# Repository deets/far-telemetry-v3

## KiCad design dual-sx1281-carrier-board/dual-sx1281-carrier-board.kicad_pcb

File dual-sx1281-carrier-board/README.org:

#+STARTUP: inlineimages showall
* Dual Carrier Board

[[file:assets/dual-sx1281-carrier-board.png]]

** PCB
*** Aisler

 - [[https://community.aisler.net/t/2-layer-1-6mm-35-m-enig-design-rules/3732][Design rules]].

** Breadboard Setup

*** E28-2G4M20SX

|------------+---------------------+----------|
| Module Pin | Breakout Pin Number | Function |
|------------+---------------------+----------|
|          1 |                  17 | 3V3      |
|          2 |                  18 | GND      |
|          3 |                  19 | SPI TX   |
|          4 |                  20 | SPI RX   |
|          5 |                  21 | SPI CLK  |
|          6 |                  22 | SPI CS   |
|          7 |                  23 | GND      |
|          8 |                  24 | RX_EN    |
|          9 |                   1 | TX_EN    |
|         10 |                   2 | GND      |
|         11 |                   3 | NRST     |
|         12 |                   4 | BUSY     |
|         13 |                   5 | IRQ      |
|         14 |                   6 | X        |
|         15 |                   7 | X        |
|         16 |                   8 | GND      |
|------------+---------------------+----------|

*** RP2040/PicoW

|------------+-----------+-------------|
| RP2040 GIO | PicoW Pin | Function    |
|------------+-----------+-------------|
|          2 |         4 | SPI0_CLK    |
|          3 |         5 | SPI0_TX     |
|          4 |         6 | SPI0_RX     |
|          5 |         7 | SPI0_CS     |
|          6 |         9 | LORA1_IRQ   |
|          7 |        10 | LORA1_BUSY  |
|          8 |        11 | LORA1_NRST  |
|          9 |        12 | LORA1_TX_EN |
|         10 |        14 | LORA1_RX_EN |
|------------+-----------+-------------|
|         11 |        15 | SPI1_TX     |
|         12 |        16 | SPI1_RX     |
|         13 |        17 | SPI1_CS     |
|         14 |        19 | SPI1_CLK    |
|         15 |        20 | LORA2_RX_EN |
|         16 |        21 | LORA2_IRQ   |
|         17 |        22 | LORA2_BUSY  |
|         18 |        24 | LORA2_NRST  |
|         19 |        25 | LORA2_TX_EN |
|------------+-----------+-------------|

[[file:assets/picow-pinout.svg]]

*** lora-phy driver implementation

**** RadioLib commands

OpCode: GetPacketType -> [03, 00, 00, ]
OpCode: GetPacketType -> [03, 00, 00, ]
OpCode: ReadRegister -> [19, 09, 3C, 00, 00, ]
OpCode: GetStatus -> [C0, 00, 00, ]
OpCode: GetPacketType -> [03, 00, 00, ]
OpCode: GetPacketType -> [03, 00, 00, ]
OpCode: GetPacketType -> [03, 00, 00, ]
OpCode: SetPacketParams -> [8C, 14, 00, FF, 20, 40, 00, 00, ]
success!
[SX1280] Transmitting packet ... OpCode: GetPacketType -> [03, 00, 00, ]
OpCode: NoOp -> [00, ]
OpCode: SetStandby -> [80, 00, ]
OpCode: GetPacketType -> [03, 00, 00, ]
OpCode: GetPacketType -> [03, 00, 00, ]
OpCode: SetPacketParams -> [8C, 14, 00, 0F, 20, 40, 00, 00, ]
OpCode: SetTxParams -> [8E, 1C, 80, ]
OpCode: SetBufferBaseAddress -> [8F, 00, 00, ]
OpCode: WriteBuffer -> [1A, 00, 48, 65, 6C, 6C, 6F, 20, 57, 6F, 72, 6C, 64, 21, 20, 23, 30, ]
OpCode: SetDioIrqParams -> [8D, 40, 01, 00, 01, 00, 00, 00, 00, ]
OpCode: SetTx -> [83, 00, 00, 00, ]

**** lora-phy translation

***** impl Lora<RK, DLY>::init

  - [X] reset
  - [X] ensure_ready
  - [X] set_standby
  - [ ] ensure_ready can't read the FirmwareVersions string, as it's used later as well. Try and make it work after reset or so.

***** impl Lora<RK, DLY>::prepare_for_tx

    - [X] self.prepare_modem(mdltn_params.frequency_in_hz).await?;
    - [X] self.radio_kind.set_modulation_params(mdltn_params).await?;
    - [ ] self.radio_kind.set_tx_power_and_ramp_time(output_power, Some(mdltn_params), true).await?;
    - [ ] self.radio_kind.ensure_ready(self.radio_mode).await?;
    - [ ] if self.radio_mode != RadioMode::Standby { self.radio_kind.set_standby().await?; self.radio_mode = RadioMode::Standby;  }
    - [ ] tx_pkt_params.set_payload_length(buffer.len())?;
    - [ ] self.radio_kind.set_packet_params(tx_pkt_params).await?;
    - [ ] self.radio_kind.set_channel(mdltn_params.frequency_in_hz).await?;
    - [ ] self.radio_kind.set_payload(buffer).await?;
    - [ ] self.radio_mode = RadioMode::Transmit;
    - [ ] self.radio_kind.set_irq_params(Some(self.radio_mode)).await?;

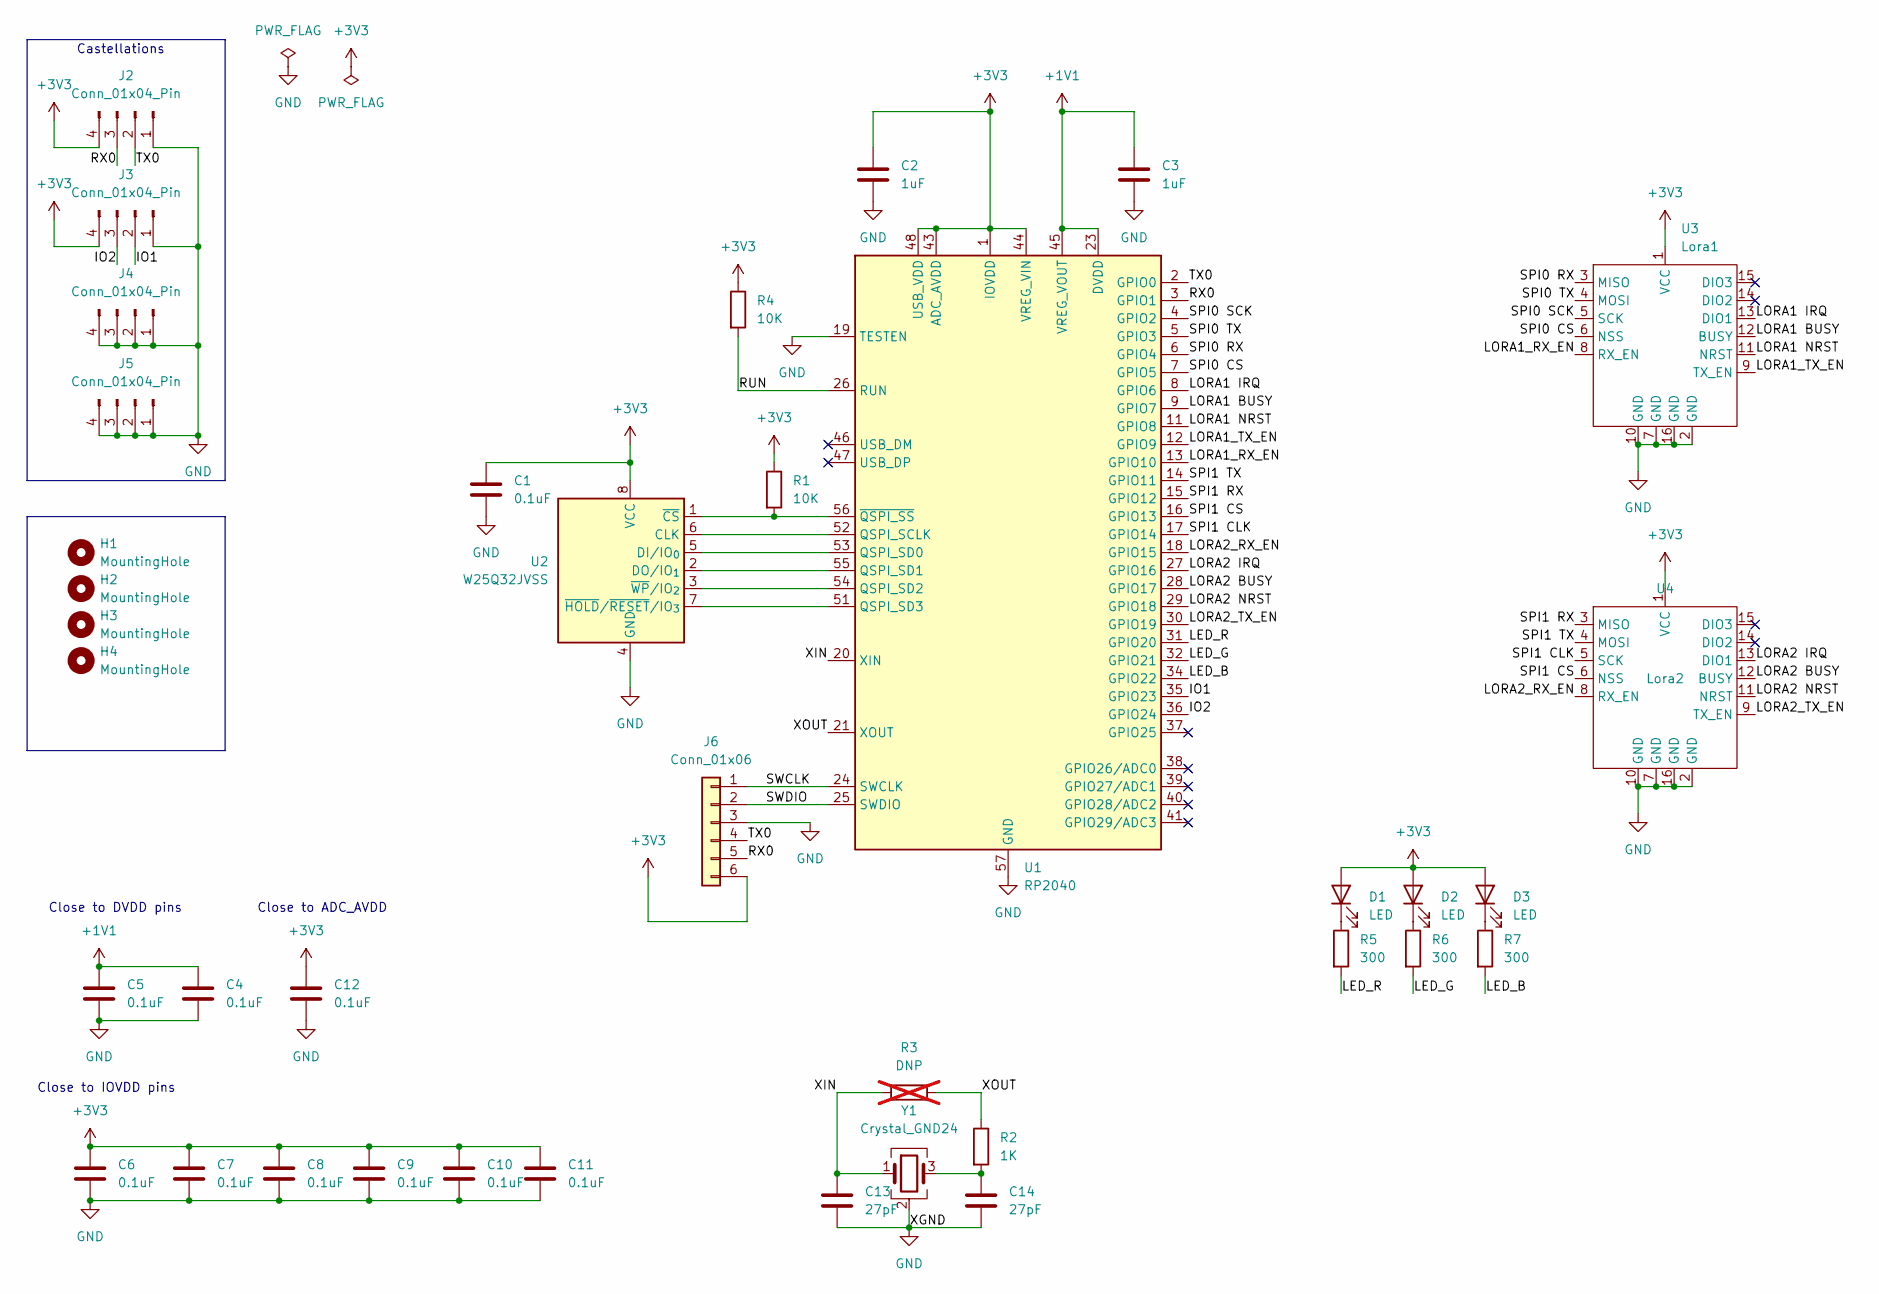
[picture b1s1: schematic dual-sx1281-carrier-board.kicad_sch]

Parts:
C1, C4, C5, C6, C7, C8, C9, C10, C11, C12: 0.1uF; C_0603_1608Metric
C2, C3: 1uF; C_0603_1608Metric
C13, C14: 27pF; C_0603_1608Metric
D1, D2, D3: LED; LED_0603_1608Metric
H1, H2, H3, H4: MountingHole; MountingHole_2mm
J2, J3, J4, J5: Conn_01x04_Pin; PinHeader_1x04_P2.54mm_Vertical
J6: Conn_01x06; Molex_PicoBlade_53398-0671_1x06-1MP_P1.25mm_Vertical
R1: 10K; R_0402_1005Metric
R2: 1K; R_0402_1005Metric
R3: DNP; R_0402_1005Metric; not fitted
R4: 10K; R_0603_1608Metric
R5, R6, R7: 300; R_0603_1608Metric
U1: RP2040; QFN-56-1EP_7x7mm_P0.4mm_EP3.2x3.2mm
U2: W25Q32JVSS; SOIC-8_5.3x5.3mm_P1.27mm
U3, U4: E28-2G4M20SX
Y1: Crystal_GND24; Crystal_SMD_3225-4Pin_3.2x2.5mm

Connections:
+1V1: C3.1, C4.1, C5.1, U1.23 (DVDD), U1.45 (VREG_VOUT), U1.50 (DVDD)
+3V3: C1.1, C2.1, C6.1, C7.1, C8.1, C9.1, C10.1, C11.1, C12.1, D1.2 (A), D2.2 (A), D3.2 (A), J2.4, J3.4, J6.6, R1.1, R4.1, U1.1 (IOVDD), U1.10 (IOVDD), U1.22 (IOVDD), U1.33 (IOVDD), U1.42 (IOVDD), U1.43 (ADC_AVDD), U1.44 (VREG_VIN), U1.48 (USB_VDD), U1.49 (IOVDD), U2.8 (VCC), U3.1 (VCC), U4.1 (VCC)
/IO1: J3.2, U1.35 (GPIO23)
/IO2: J3.3, U1.36 (GPIO24)
/LED_B: R7.2, U1.34 (GPIO22)
/LED_G: R6.2, U1.32 (GPIO21)
/LED_R: R5.2, U1.31 (GPIO20)
/LORA1 BUSY: U1.9 (GPIO7), U3.12 (BUSY)
/LORA1 IRQ: U1.8 (GPIO6), U3.13 (DIO1)
/LORA1 NRST: U1.11 (GPIO8), U3.11 (NRST)
/LORA1_RX_EN: U1.13 (GPIO10), U3.8 (RX_EN)
/LORA1_TX_EN: U1.12 (GPIO9), U3.9 (TX_EN)
/LORA2 BUSY: U1.28 (GPIO17), U4.12 (BUSY)
/LORA2 IRQ: U1.27 (GPIO16), U4.13 (DIO1)
/LORA2 NRST: U1.29 (GPIO18), U4.11 (NRST)
/LORA2_RX_EN: U1.18 (GPIO15), U4.8 (RX_EN)
/LORA2_TX_EN: U1.30 (GPIO19), U4.9 (TX_EN)
/RUN: R4.2, U1.26 (RUN)
/RX0: J2.3, J6.5, U1.3 (GPIO1)
/SPI0 CS: U1.7 (GPIO5), U3.6 (NSS)
/SPI0 RX: U1.6 (GPIO4), U3.3 (MISO)
/SPI0 SCK: U1.4 (GPIO2), U3.5 (SCK)
/SPI0 TX: U1.5 (GPIO3), U3.4 (MOSI)
/SPI1 CLK: U1.17 (GPIO14), U4.5 (SCK)
/SPI1 CS: U1.16 (GPIO13), U4.6 (NSS)
/SPI1 RX: U1.15 (GPIO12), U4.3 (MISO)
/SPI1 TX: U1.14 (GPIO11), U4.4 (MOSI)
/SWCLK: J6.1, U1.24 (SWCLK)
/SWDIO: J6.2, U1.25 (SWDIO)
/TX0: J2.2, J6.4, U1.2 (GPIO0)
/XIN: C13.1, R3.1, U1.20 (XIN), Y1.1
/XOUT: R2.1, R3.2, U1.21 (XOUT)
GND: C1.2, C2.2, C3.2, C4.2, C5.2, C6.2, C7.2, C8.2, C9.2, C10.2, C11.2, C12.2, C13.2, C14.2, J2.1, J3.1, J4.1, J4.2, J4.3, J4.4, J5.1, J5.2, J5.3, J5.4, J6.3, U1.19 (TESTEN), U1.57 (GND), U2.4 (GND), U3.2 (GND), U3.7 (GND), U3.10 (GND), U3.16 (GND), U4.2 (GND), U4.7 (GND), U4.10 (GND), U4.16 (GND), Y1.2 (G), Y1.4 (G)
unnamed: C14.1, R2.2, Y1.3
unnamed: D1.1 (K), R5.1
unnamed: D2.1 (K), R6.1
unnamed: D3.1 (K), R7.1
unnamed: U1.52 (QSPI_SCLK), U2.6 (CLK)
unnamed: U1.53 (QSPI_SD0), U2.5 (DI/IO_{0})
unnamed: U1.55 (QSPI_SD1), U2.2 (DO/IO_{1})
unnamed: U1.54 (QSPI_SD2), U2.3 (~WP/IO_{2})
unnamed: U1.51 (QSPI_SD3), U2.7 (~HOLD/~RESET/IO_{3})
unnamed: R1.2, U1.56 (~QSPI_SS), U2.1 (~CS)

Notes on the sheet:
Castellations
Close to ADC_AVDD
Close to DVDD pins
Close to IOVDD pins

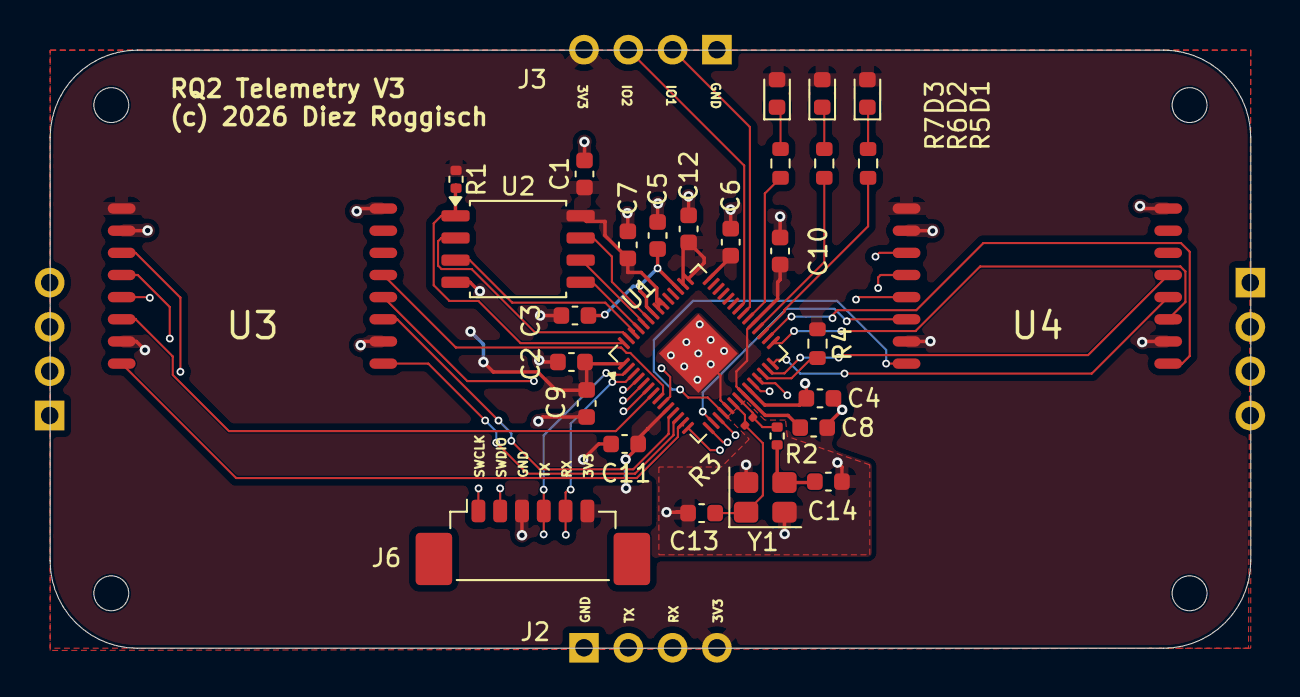
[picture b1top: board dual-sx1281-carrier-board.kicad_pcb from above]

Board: 4 copper layers, 68.8 x 34.3 mm, 38 parts (0 on the bottom side), 43 nets.

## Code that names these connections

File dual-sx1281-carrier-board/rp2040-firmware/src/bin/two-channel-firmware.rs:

//! This example runs on the Raspberry Pi Pico with a Waveshare board containing a Semtech Sx1262 radio.
//! It demonstrates LORA P2P send functionality.

#![no_std]
#![no_main]

use defmt::*;
use dual_sx1281_carrier_board::MessageType;
use dual_sx1281_carrier_board::{
    host_interface::uart_task, lora1_task, lora2_task, LORA1_PAYLOAD_RECEIVE_CHANNEL,
    LORA1_PAYLOAD_SEND_CHANNEL, LORA1_RECEIVE_CHANNEL, LORA1_SEND_CHANNEL,
    LORA2_PAYLOAD_RECEIVE_CHANNEL, LORA2_PAYLOAD_SEND_CHANNEL, LORA2_RECEIVE_CHANNEL,
    LORA2_SEND_CHANNEL,
};
use embassy_executor::Spawner;
use embassy_rp::bind_interrupts;
use embassy_rp::gpio::{Input, Level, Output, Pin, Pull};
use embassy_rp::peripherals::UART0;
use embassy_rp::spi::{Config, Spi};
use embassy_rp::uart::{Config as UartConfig, InterruptHandler, Uart};
use embassy_sync::blocking_mutex::raw::NoopRawMutex;
use embassy_sync::channel::Channel;
use embassy_time::{Delay, Timer};
use embedded_hal_bus::spi::ExclusiveDevice;
use lora_phy::iv::GenericSx128xInterfaceVariant;
use lora_phy::sx128x::{self, Sx1281, Sx128x};
use lora_phy::LoRa;
use rq2_telemetry_parser::Command;
use {defmt_rtt as _, panic_probe as _};

bind_interrupts!(struct Irqs {
    UART0_IRQ => InterruptHandler<UART0>;
});

#[embassy_executor::main]
async fn main(spawner: Spawner) {
    info!("running");
    let p = embassy_rp::init(Default::default());

    let lora1_nss = Output::new(p.PIN_5.degrade(), Level::High);
    let lora1_busy = Input::new(p.PIN_7.degrade(), Pull::None);
    let lora1_reset = Output::new(p.PIN_8.degrade(), Level::High);
    let lora1_irq = Input::new(p.PIN_6.degrade(), Pull::None);
    let lora1_rx_en = Output::new(p.PIN_10.degrade(), Level::Low);
    let lora1_tx_en = Output::new(p.PIN_9.degrade(), Level::Low);

    let (tx_pin, rx_pin, uart) = (p.PIN_0, p.PIN_1, p.UART0);
    let uart = Uart::new(
        uart,
        tx_pin,
        rx_pin,
        Irqs,
        p.DMA_CH4,
        p.DMA_CH5,
        UartConfig::default(),
    );

    let lora1_spi = Spi::new(
        p.SPI0,
        p.PIN_2,
        p.PIN_3,
        p.PIN_4,
        p.DMA_CH0,
        p.DMA_CH1,
        Config::default(),
    );
    let lora1_spi = ExclusiveDevice::new(lora1_spi, lora1_nss, Delay);
    let lora1_config = sx128x::Config {
        chip: Sx1281,
        tcxo_used: true,
        rx_boost: true,
        tx_boost: true,
    };
    let lora1_iv = GenericSx128xInterfaceVariant::new(
        lora1_reset,
        lora1_irq,
        lora1_busy,
        Some(lora1_rx_en),
        Some(lora1_tx_en),
    )
    .unwrap();
    let lora1 = LoRa::new(Sx128x::new(lora1_spi, lora1_iv, lora1_config), false, Delay)
        .await
        .unwrap();
    info!("Created lora1");

    let lora2_nss = Output::new(p.PIN_13.degrade(), Level::High);
    let lora2_busy = Input::new(p.PIN_17.degrade(), Pull::None);
    let lora2_reset = Output::new(p.PIN_18.degrade(), Level::High);
    let lora2_irq = Input::new(p.PIN_16.degrade(), Pull::None);
    let lora2_rx_en = Output::new(p.PIN_15.degrade(), Level::Low);
    let lora2_tx_en = Output::new(p.PIN_19.degrade(), Level::Low);

    let lora2_spi = Spi::new(
        p.SPI1,
        p.PIN_14,
        p.PIN_11,
        p.PIN_12,
        p.DMA_CH2,
        p.DMA_CH3,
        Config::default(),
    );

    let lora2_spi = ExclusiveDevice::new(lora2_spi, lora2_nss, Delay);
    let lora2_config = sx128x::Config {
        chip: Sx1281,
        tcxo_used: true,
        rx_boost: true,
        tx_boost: true,
    };
    let lora2_iv = GenericSx128xInterfaceVariant::new(
        lora2_reset,
        lora2_irq,
        lora2_busy,
        Some(lora2_rx_en),
        Some(lora2_tx_en),
    )
    .unwrap();
    let lora2 = LoRa::new(Sx128x::new(lora2_spi, lora2_iv, lora2_config), false, Delay)
        .await
        .unwrap();
    info!("Created lora2");

    let lora1_send_channel = Channel::<NoopRawMutex, Command, 4>::new();
    let static_lora1_send_channel = LORA1_SEND_CHANNEL.init(lora1_send_channel);
    let lora1_receive_channel = Channel::<NoopRawMutex, Command, 4>::new();
    let static_lora1_receive_channel = LORA1_RECEIVE_CHANNEL.init(lora1_receive_channel);

    let lora1_payload_send_channel = Channel::<NoopRawMutex, MessageType, 4>::new();
    let static_payload_lora1_send_channel =
        LORA1_PAYLOAD_SEND_CHANNEL.init(lora1_payload_send_channel);
    let lora1_payload_receive_channel = Channel::<NoopRawMutex, MessageType, 4>::new();
    let static_payload_lora1_receive_channel =
        LORA1_PAYLOAD_RECEIVE_CHANNEL.init(lora1_payload_receive_channel);

    let lora2_send_channel = Channel::<NoopRawMutex, Command, 4>::new();
    let static_lora2_send_channel = LORA2_SEND_CHANNEL.init(lora2_send_channel);
    let lora2_receive_channel = Channel::<NoopRawMutex, Command, 4>::new();
    let static_lora2_receive_channel = LORA2_RECEIVE_CHANNEL.init(lora2_receive_channel);

    let lora2_payload_send_channel = Channel::<NoopRawMutex, MessageType, 4>::new();
    let static_payload_lora2_send_channel =
        LORA2_PAYLOAD_SEND_CHANNEL.init(lora2_payload_send_channel);
    let lora2_payload_receive_channel = Channel::<NoopRawMutex, MessageType, 4>::new();
    let static_payload_lora2_receive_channel =
        LORA2_PAYLOAD_RECEIVE_CHANNEL.init(lora2_payload_receive_channel);

    spawner
        .spawn(lora1_task(
            lora1,
            static_lora1_send_channel.receiver(),
            static_lora1_receive_channel.sender(),
            static_payload_lora1_send_channel.receiver(),
            static_payload_lora1_receive_channel.sender(),
        ))
        .expect("Can't spawn Lora1 task");

    spawner
        .spawn(lora2_task(
            lora2,
            static_lora2_send_channel.receiver(),
            static_lora2_receive_channel.sender(),
            static_payload_lora2_send_channel.receiver(),
            static_payload_lora2_receive_channel.sender(),
        ))
        .expect("Can't spawn Lora2 task");

    uart_task(
        uart,
        static_lora1_send_channel.sender(),
        static_lora1_receive_channel.receiver(),
        static_payload_lora1_send_channel.sender(),
        static_payload_lora1_receive_channel.receiver(),
        static_lora2_send_channel.sender(),
        static_lora2_receive_channel.receiver(),
        static_payload_lora2_send_channel.sender(),
        static_payload_lora2_receive_channel.receiver(),
    )
    .await;
    loop {
        Timer::after_millis(10).await;
    }
}

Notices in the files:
dual-sx1281-carrier-board/dual-sx1281-carrier-board.kicad_pcb:
(c) 2026 Diez Roggisch
